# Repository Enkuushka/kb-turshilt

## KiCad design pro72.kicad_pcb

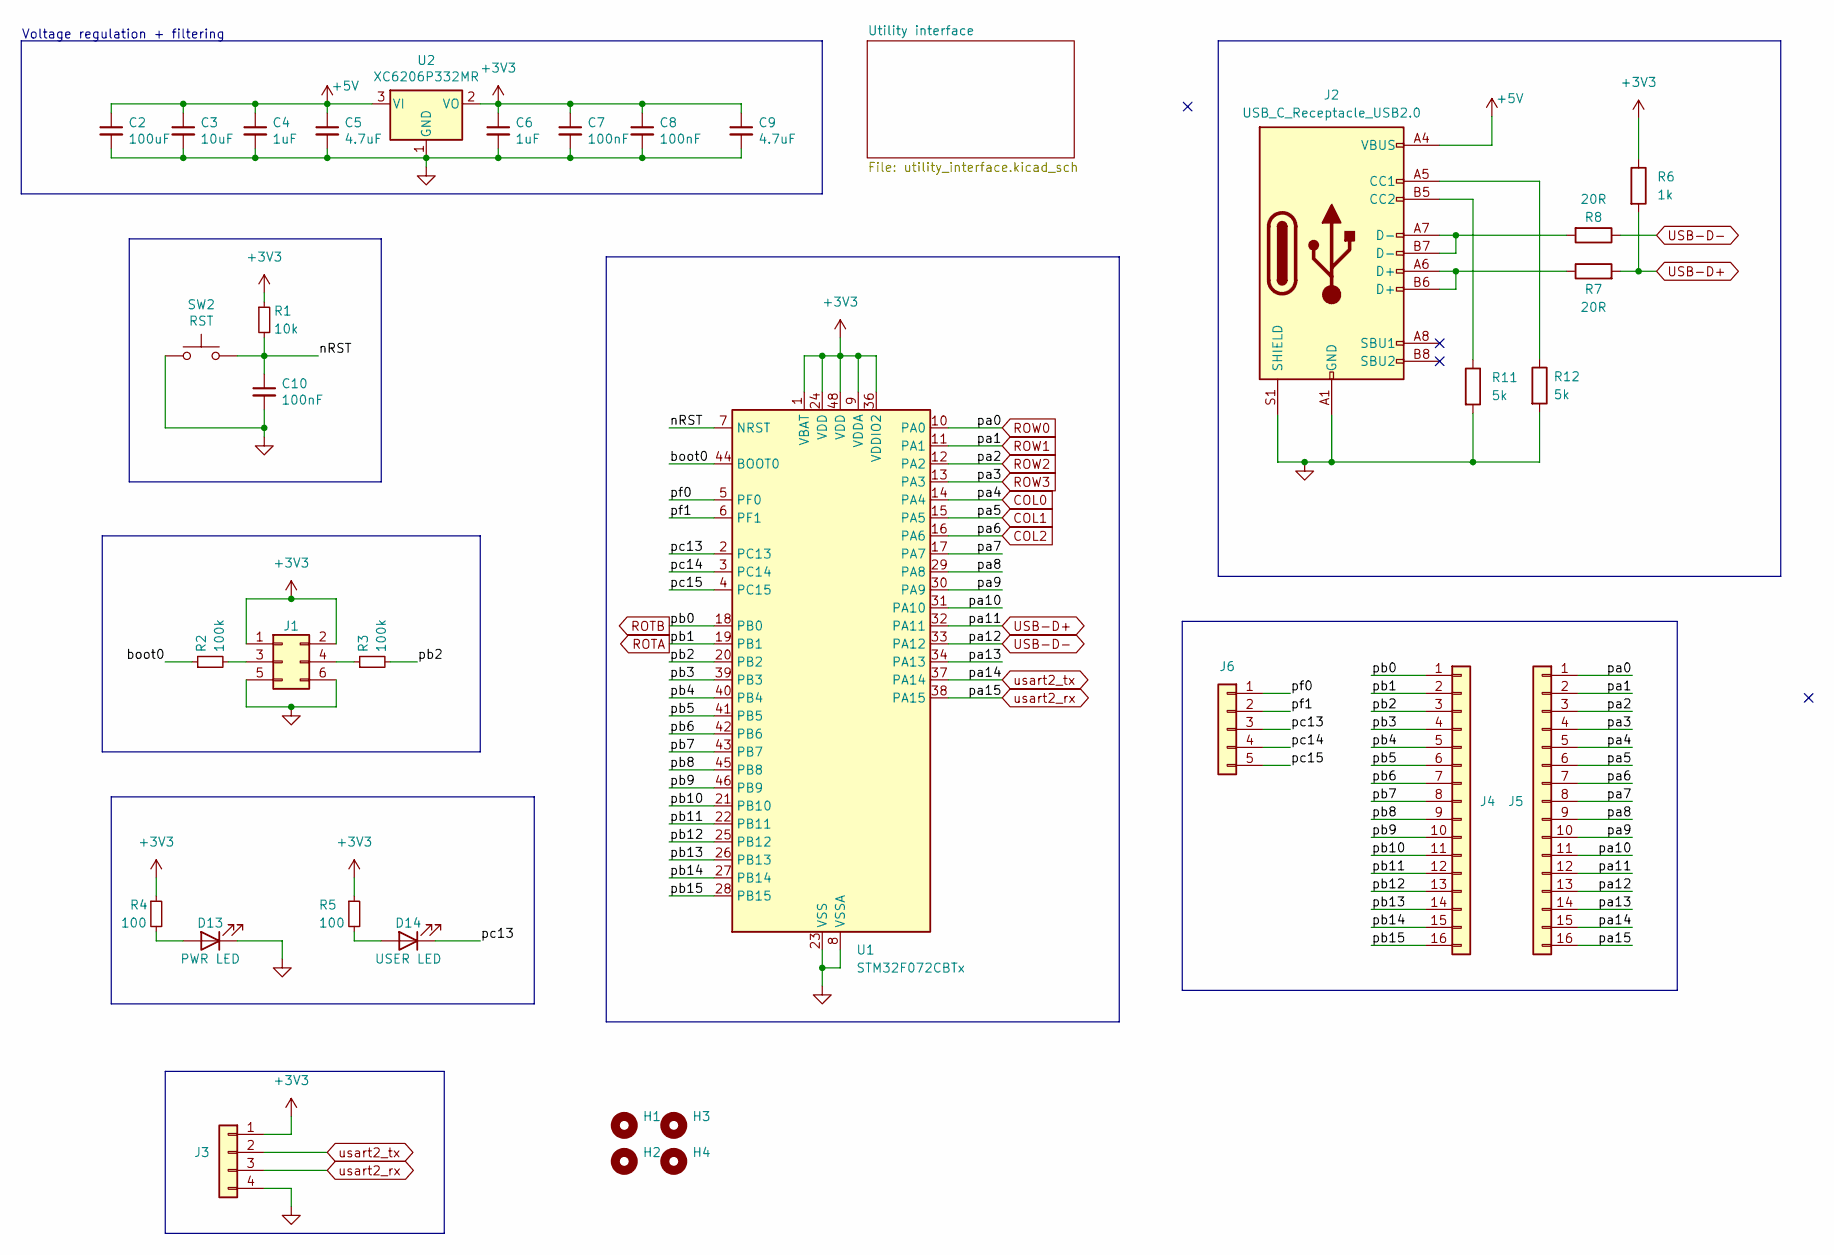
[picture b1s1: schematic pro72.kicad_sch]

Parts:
C2: 100uF; C_0402_1005Metric; LCSC C16133
C3: 10uF; C_0402_1005Metric; LCSC C7171
C4, C6: 1uF; C_0402_1005Metric; LCSC C52923
C5, C9: 4.7uF; C_0402_1005Metric; LCSC C23733
C7, C8, C10: 100nF; C_0402_1005Metric; LCSC C1525
D13: PWR LED; LED_0201_0603Metric
D14: USER LED; LED_0201_0603Metric
H1, H2, H3, H4: MountingHole; MountingHole_2.7mm_M2.5
J1: BOOT_SELECTION_JUMPER; PinHeader_2x03_P2.54mm_Vertical
J2: USB_C_Receptacle_USB2.0; USB_C_Receptacle_G-Switch_GT-USB-7010ASV
J3: Conn_01x04; PinHeader_1x04_P2.54mm_Vertical
J4, J5: Conn_01x16; PinHeader_1x16_P2.54mm_Vertical
J6: Conn_01x05; PinHeader_1x05_P2.54mm_Vertical
R1: 10k; R_0402_1005Metric; LCSC C25744
R2, R3: 100k; R_0402_1005Metric; LCSC C25744
R4, R5: 100; R_0402_1005Metric; LCSC C25744
R6: 1k; R_0402_1005Metric
R7, R8: 20R; R_0402_1005Metric
R11, R12: 5k; R_0402_1005Metric
SW2: RST; SW_SPST_SKQG_WithStem; LCSC C318886
U1: STM32F072CBTx; LQFP-48_7x7mm_P0.5mm
U2: XC6206P332MR; SOT-23; LCSC C5446

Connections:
+3V3: C6.1, C7.1, C8.1, C9.1, J1.1, J1.2, J3.1, R1.1, R4.1, R5.1, R6.1, U1.1 (VBAT), U1.9 (VDDA), U1.24 (VDD), U1.36 (VDDIO2), U1.48 (VDD), U2.2 (VO); also elsewhere on the board
+5V: C2.1, C3.1, C4.1, C5.1, J2.A4 (VBUS), J2.A9 (VBUS), J2.B4 (VBUS), J2.B9 (VBUS), U2.3 (VI)
/boot0: R2.1, U1.44 (BOOT0)
/nRST: C10.1, R1.2, SW2.2, U1.7 (NRST)
/pa7: J5.8, U1.17 (PA7)
/pa8: J5.9, U1.29 (PA8)
/pa9: J5.10, U1.30 (PA9)
/pa10: J5.11, U1.31 (PA10)
/pa13: J5.14, U1.34 (PA13)
/pb2: J4.3, R3.2, U1.20 (PB2)
/pb3: J4.4, U1.39 (PB3)
/pb4: J4.5, U1.40 (PB4)
/pb5: J4.6, U1.41 (PB5)
/pb6: J4.7, U1.42 (PB6)
/pb7: J4.8, U1.43 (PB7)
/pb8: J4.9, U1.45 (PB8)
/pb9: J4.10, U1.46 (PB9)
/pb10: J4.11, U1.21 (PB10)
/pb11: J4.12, U1.22 (PB11)
/pb12: J4.13, U1.25 (PB12)
/pb13: J4.14, U1.26 (PB13)
/pb14: J4.15, U1.27 (PB14)
/pb15: J4.16, U1.28 (PB15)
/pc13: D14.1 (K), J6.3, U1.2 (PC13)
/pc14: J6.4, U1.3 (PC14)
/pc15: J6.5, U1.4 (PC15)
/pf0: J6.1, U1.5 (PF0)
/pf1: J6.2, U1.6 (PF1)
COL0: J5.5, U1.14 (PA4); also elsewhere on the board
COL1: J5.6, U1.15 (PA5); also elsewhere on the board
COL2: J5.7, U1.16 (PA6); also elsewhere on the board
GND: C2.2, C3.2, C4.2, C5.2, C6.2, C7.2, C8.2, C9.2, C10.2, D13.1 (K), J1.5, J1.6, J2.A1 (GND), J2.A12 (GND), J2.B1 (GND), J2.B12 (GND), J2.S1 (SHIELD), J3.4, R11.2, R12.2, SW2.1, U1.8 (VSSA), U1.23 (VSS), U1.35 (VSS), U1.47 (VSS), U2.1 (GND); also elsewhere on the board
unnamed: D13.2 (A), R4.2
unnamed: D14.2 (A), R5.2
unnamed: J1.3, R2.2
unnamed: J1.4, R3.1
unnamed: J2.A5 (CC1), R12.1
unnamed: J2.B5 (CC2), R11.1
unnamed: J2.A6 (D+), J2.B6 (D+), R7.1
unnamed: J2.A7 (D-), J2.B7 (D-), R8.2
ROTA: J4.2, U1.19 (PB1); also elsewhere on the board
ROTB: J4.1, U1.18 (PB0); also elsewhere on the board
ROW0: J5.1, U1.10 (PA0); also elsewhere on the board
ROW1: J5.2, U1.11 (PA1); also elsewhere on the board
ROW2: J5.3, U1.12 (PA2); also elsewhere on the board
ROW3: J5.4, U1.13 (PA3); also elsewhere on the board
USB-D+: J5.12, R6.2, R7.2, U1.32 (PA11)
USB-D-: J5.13, R8.1, U1.33 (PA12)
usart2_rx: J3.3, J5.16, U1.38 (PA15)
usart2_tx: J3.2, J5.15, U1.37 (PA14)

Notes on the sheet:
Voltage regulation + filtering

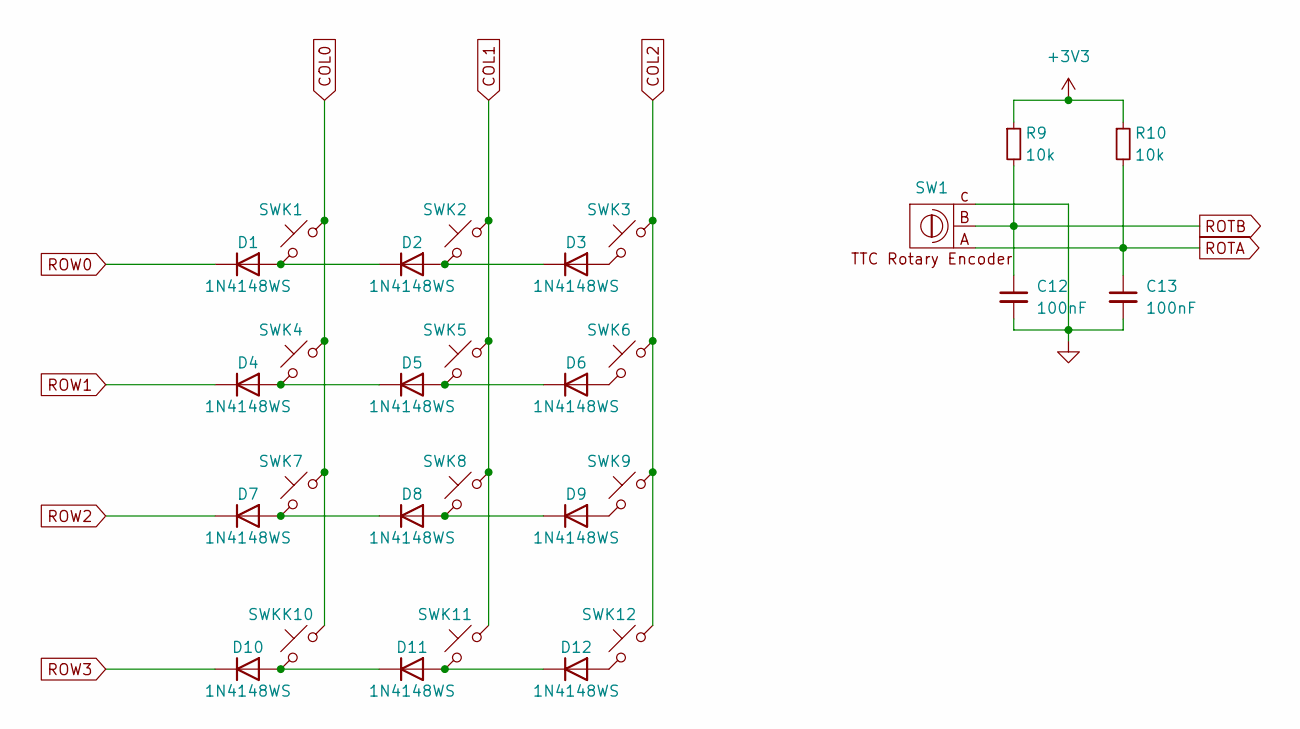
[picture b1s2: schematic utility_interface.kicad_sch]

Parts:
C12, C13: 100nF; C_0402_1005Metric; LCSC C1525
D1, D2, D3, D4, D5, D6, D7, D8, D9, D10, D11, D12: 1N4148WS; D_SOD-323
R9, R10: 10k; R_0402_1005Metric; LCSC C25744
SW1: e103-07
SWK1, SWK8: SW_Cherry_MX_1.00u_PCB
SWK2, SWK11: KEY2; SW_Cherry_MX_1.00u_PCB
SWK3, SWK12: KEY3; SW_Cherry_MX_1.00u_PCB
SWK4: KEY4; SW_Cherry_MX_1.00u_PCB
SWK5: KEY5; SW_Cherry_MX_1.00u_PCB
SWK6, SWK9: KEY6; SW_Cherry_MX_1.00u_PCB
SWK7: KEY7; SW_Cherry_MX_1.00u_PCB
SWKK10: KEY1; SW_Cherry_MX_1.00u_PCB

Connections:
+3V3: R9.1, R10.1; also elsewhere on the board
COL0: SWK1.1, SWK4.1, SWK7.1, SWKK10.1; also elsewhere on the board
COL1: SWK2.1, SWK5.1, SWK8.1, SWK11.1; also elsewhere on the board
COL2: SWK3.1, SWK6.1, SWK9.1, SWK12.1; also elsewhere on the board
GND: C12.2, C13.2, SW1.C (3); also elsewhere on the board
unnamed: D1.2 (A), D2.1 (K), SWK1.2
unnamed: D2.2 (A), D3.1 (K), SWK2.2
unnamed: D3.2 (A), SWK3.2
unnamed: D4.2 (A), D5.1 (K), SWK4.2
unnamed: D5.2 (A), D6.1 (K), SWK5.2
unnamed: D6.2 (A), SWK6.2
unnamed: D7.2 (A), D8.1 (K), SWK7.2
unnamed: D8.2 (A), D9.1 (K), SWK8.2
unnamed: D9.2 (A), SWK9.2
unnamed: D10.2 (A), D11.1 (K), SWKK10.2
unnamed: D11.2 (A), D12.1 (K), SWK11.2
unnamed: D12.2 (A), SWK12.2
ROTA: C13.1, R10.2, SW1.A (1); also elsewhere on the board
ROTB: C12.1, R9.2, SW1.B (2); also elsewhere on the board
ROW0: D1.1 (K); also elsewhere on the board
ROW1: D4.1 (K); also elsewhere on the board
ROW2: D7.1 (K); also elsewhere on the board
ROW3: D10.1 (K); also elsewhere on the board

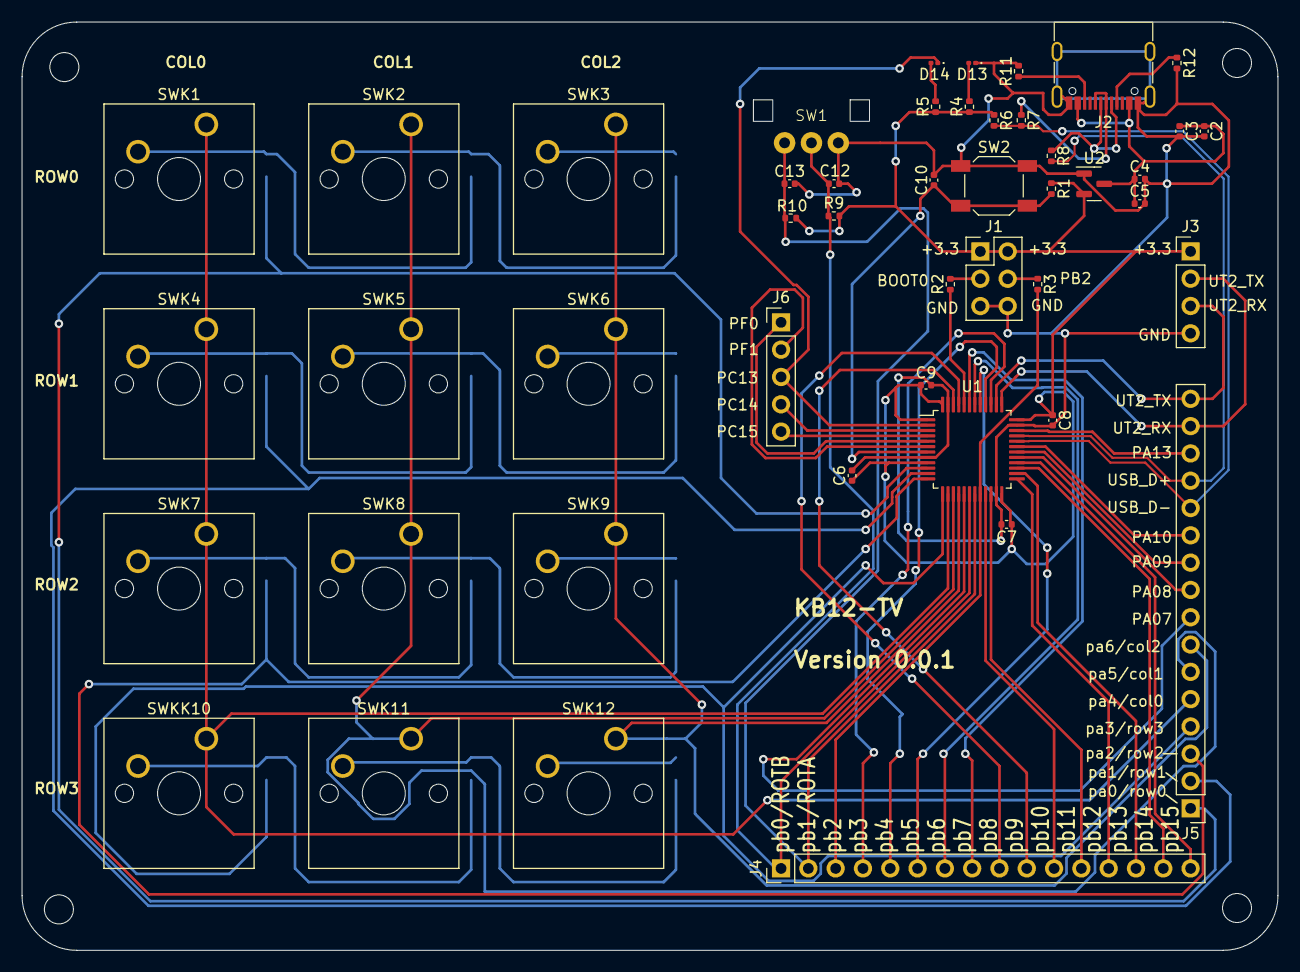
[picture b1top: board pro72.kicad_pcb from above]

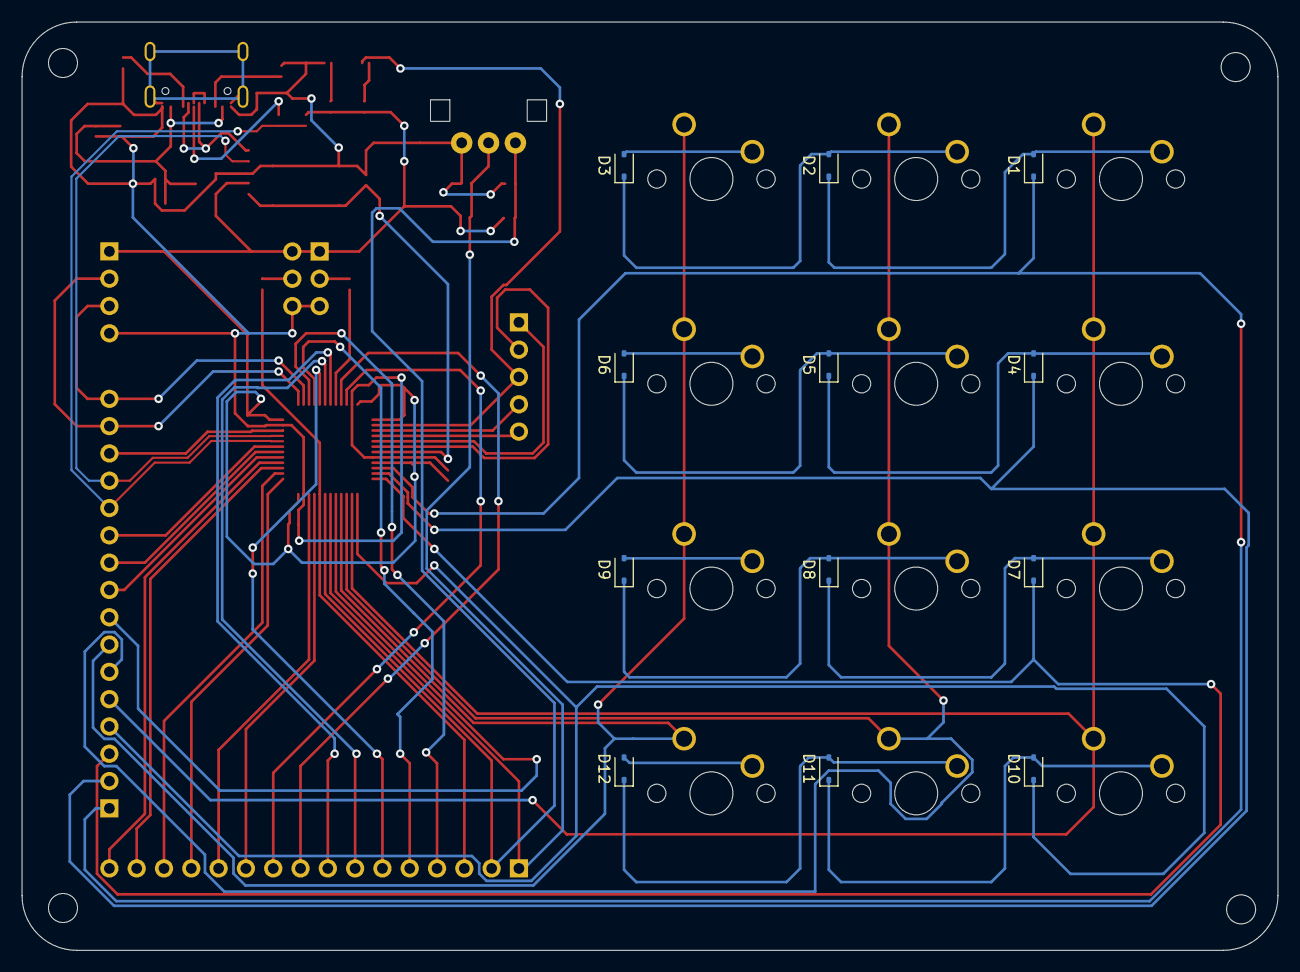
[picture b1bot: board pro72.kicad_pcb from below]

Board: 2 copper layers, 116.8 x 86.4 mm, 63 parts (12 on the bottom side), 62 nets.

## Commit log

2023-09-19 init
